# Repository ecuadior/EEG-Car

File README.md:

# EEG-Car
Project on a small car being controlled by ones brain wave 

UPDATES will be weekly/bi-weekly depends on school

  Currently working on the project I'll be posting the steps I've done to create this project. I'll use microcontrollers to read the brain wave and move the car. The plan is to create a PCB for the vehicle.

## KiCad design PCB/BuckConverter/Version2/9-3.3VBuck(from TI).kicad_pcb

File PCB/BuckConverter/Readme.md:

Buck converter that will be used to power the esp 32 board
9 to 3.3V
current max output: 300mA

WHile testing out the pcb for the buck converter it was found out there was no output volatge/current. Debugging was done with a multimeter testing whih component recive voltage and testing if there is any short circuirt by testing contiuity. 
During the test it was found there was no error short shirt becasue the contituty was acting cirrectly for all componet. While looking for components volatge it was found everything to the right of the IC was recing voltge but ervrything to the left wasnt recving volatge. I speculate it could be the EN pin connected to the voolatge divder, in which the path is to small that signal is not passing. More so, the data sheet for LMR36503 highlits that in some case the EN pin should be connected starigh to VIN. 

Another possible issue is the instalation of yhe inductor to the pcb it might have damage something because when testing the connectvity of where the inductor will be place there is no noise(indacting contiuity is good) but this was with testing on the pcb with no componet. Howeverm doing the same test with the pcb with componets continutyi was found beteern the two ends of the the inductor. 
Image below is version 1 of the buck converter

Buck Converter V2 during testing showcased outstanding result,s in which it was able to deliver the optimal output and was able to withstand the increase of temparutre during usage.

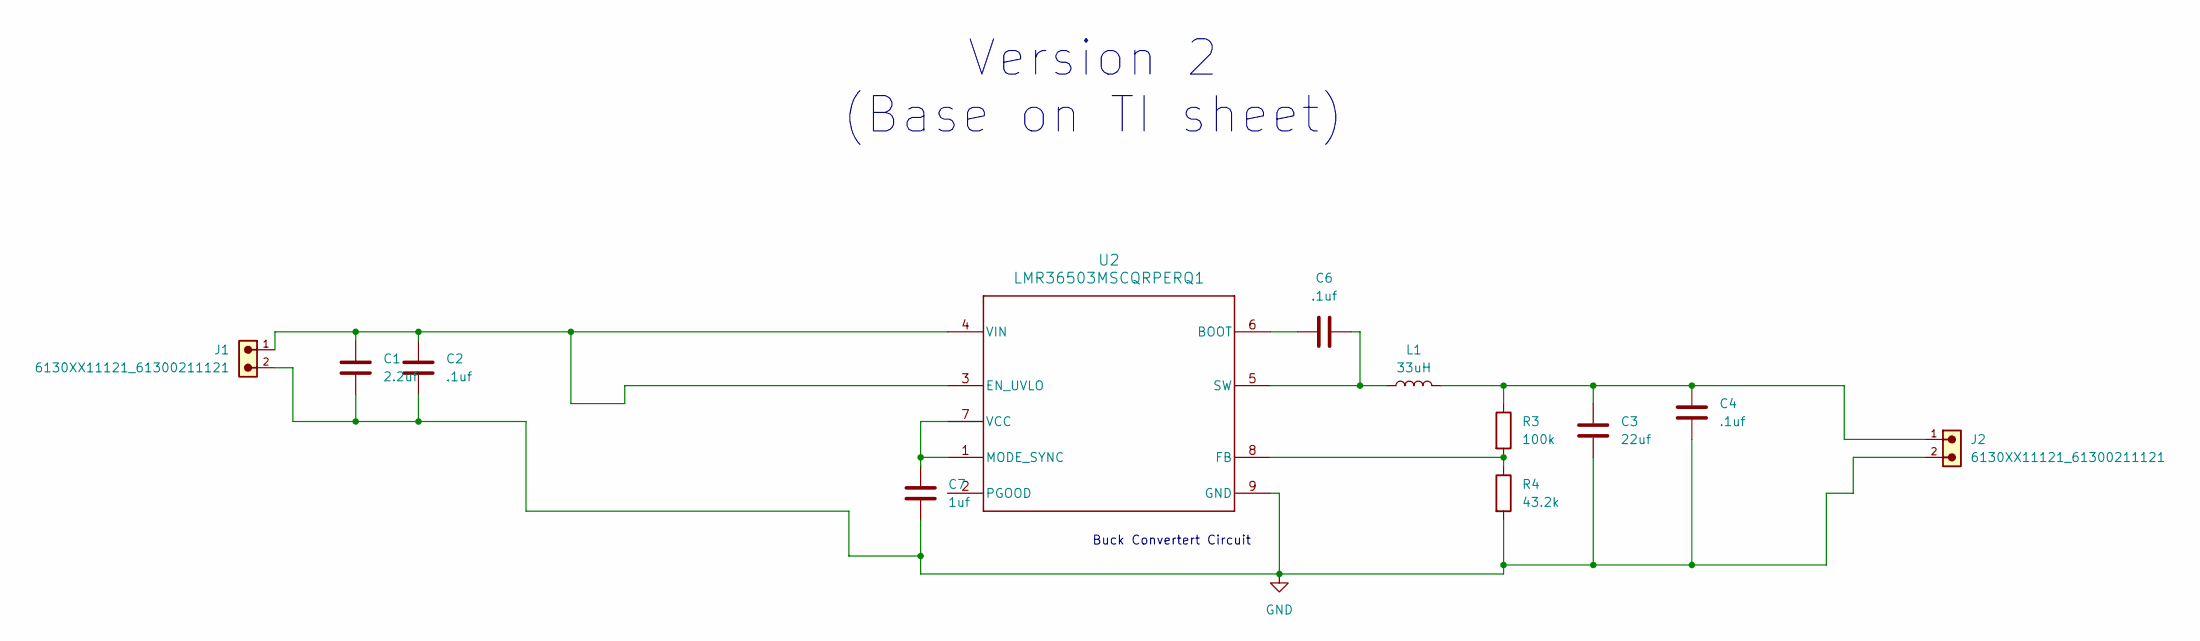
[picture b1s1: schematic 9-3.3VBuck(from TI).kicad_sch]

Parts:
C1: 2.2uf; C_0805_2012Metric; LCSC C125847
C2, C4, C6: .1uf; C_0603_1608Metric; LCSC C30926
C3: 22uf; CAPC3225X270N; LCSC C126614
C7: 1uf; C_0603_1608Metric; LCSC C93816
J1, J2: 6130XX11121_61300211121; 61300211121
L1: 33uH; IND_SRR6038-330Y; LCSC C2041395
R3: 100k; RESC1607X60N; LCSC C14675
R4: 43.2k; R_0603_1608Metric
U2: LMR36503MSCQRPERQ1; RPE0009A; LCSC C3190190

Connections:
GND: C1.2, C2.2, C3.2, C4.2, C7.2, J1.2, J2.2, R4.2, U2.9 (GND)
unnamed: C3.1, C4.1, J2.1, L1.2, R3.1
unnamed: C6.1, U2.6 (BOOT)
unnamed: C1.1, C2.1, J1.1, U2.3 (EN_UVLO), U2.4 (VIN)
unnamed: R3.2, R4.1, U2.8 (FB)
unnamed: C7.1, U2.1 (MODE_SYNC), U2.7 (VCC)
unnamed: C6.2, L1.1, U2.5 (SW)

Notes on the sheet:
Buck Convertert Circuit
Version 2 (Base on TI sheet)

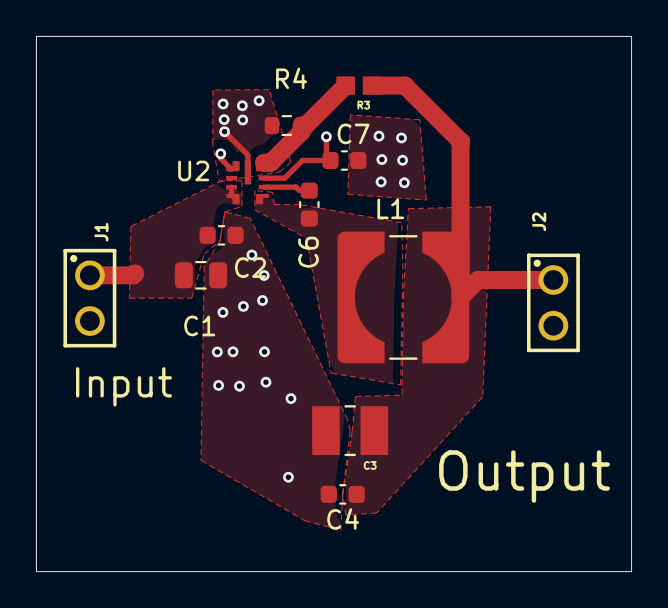
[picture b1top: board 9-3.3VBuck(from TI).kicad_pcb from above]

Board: 4 copper layers, 33.1 x 29.7 mm, 12 parts (0 on the bottom side), 7 nets.

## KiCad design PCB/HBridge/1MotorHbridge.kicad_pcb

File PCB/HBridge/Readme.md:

H bridge used to control the motor that will move the car. 

Schematic Image

PCB Image:

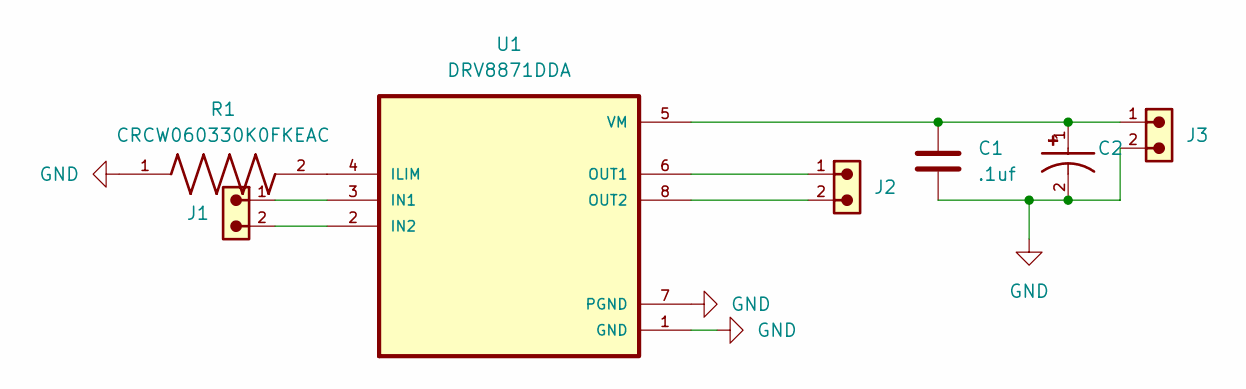
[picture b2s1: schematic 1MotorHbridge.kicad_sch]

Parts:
C1: .1uf; C_0603_1608Metric
C2: EEHZC1V470P; CAP_EEHZC1V470P; PARTREV 30-Sep-20; DigiKey_Part_Number P15473TR-ND
J1, J2, J3: 6130XX11121_61300211121; 61300211121
R1: CRCW060330K0FKEAC; RESC1608X55N
U1: DRV8871DDA; VREG_LM5017MR_NOPB

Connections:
GND: C1.2, C2.2, J3.2, R1.1, U1.1 (GND), U1.7 (PGND)
unnamed: R1.2, U1.4 (ILIM)
unnamed: J1.1, U1.3 (IN1)
unnamed: J1.2, U1.2 (IN2)
unnamed: J2.1, U1.6 (OUT1)
unnamed: J2.2, U1.8 (OUT2)
unnamed: C1.1, C2.1, J3.1, U1.5 (VM)

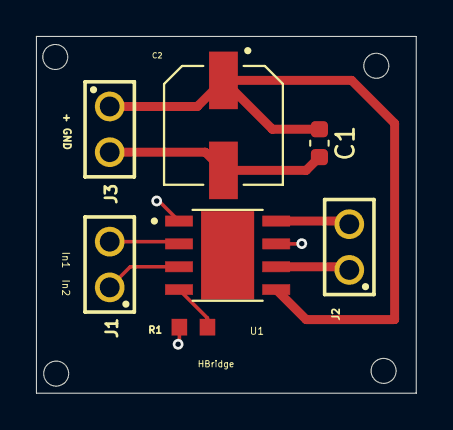
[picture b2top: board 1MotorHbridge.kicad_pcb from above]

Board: 2 copper layers, 21.1 x 19.8 mm, 7 parts (0 on the bottom side), 7 nets.

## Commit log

2025-01-29 upload code for slave esp32
2025-07-17 Rename PCB/BuckConverter/Buck Converter.kicad_pro to PCB/BuckConverter/Version1/Buck Converter.kicad_pro
2025-08-05 Buck convert V2
